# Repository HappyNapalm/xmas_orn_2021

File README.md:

# xmas_orn_2021
Repo for 2021 Ornament Design Files and Firmware

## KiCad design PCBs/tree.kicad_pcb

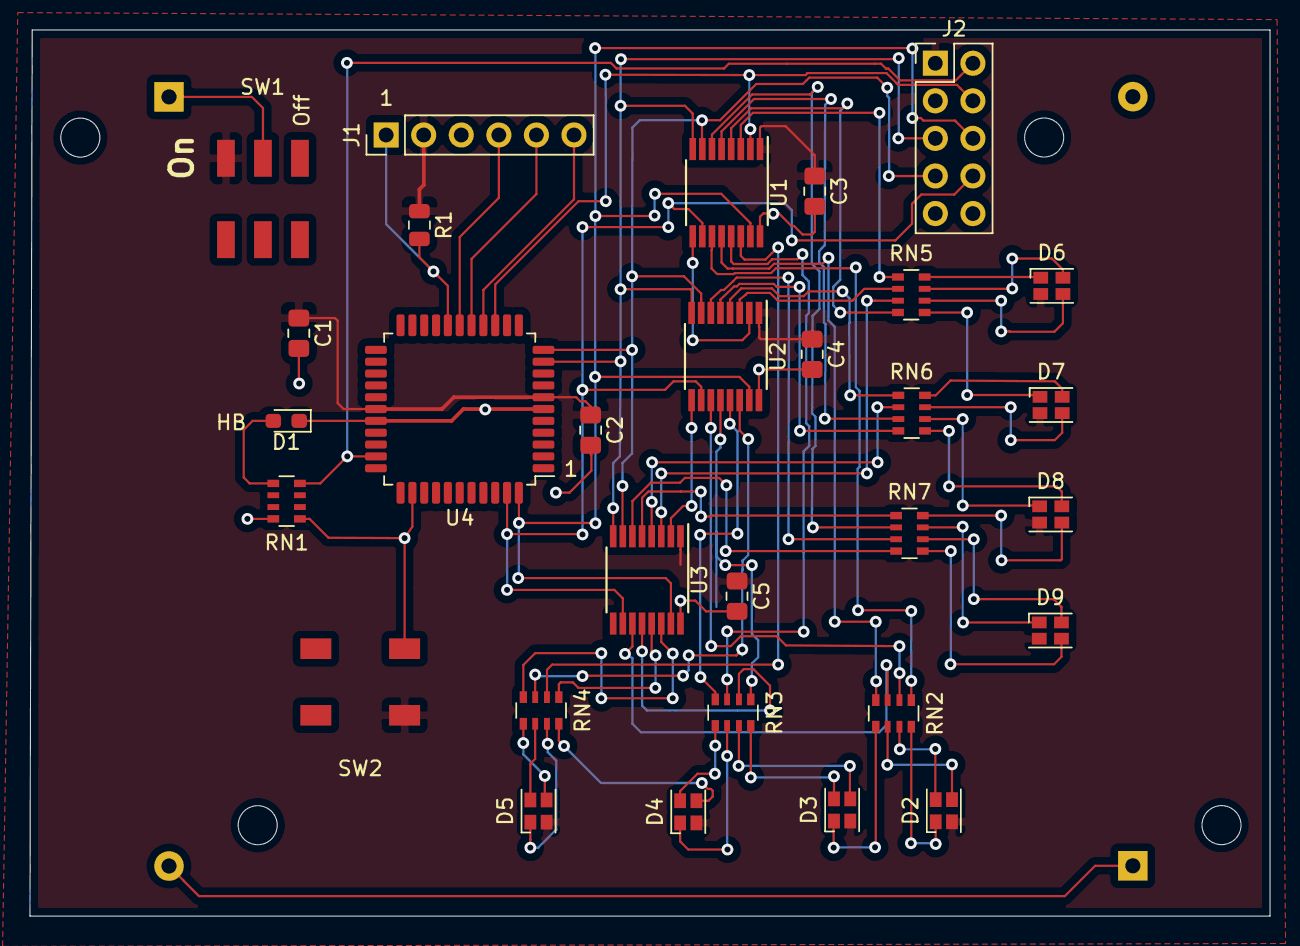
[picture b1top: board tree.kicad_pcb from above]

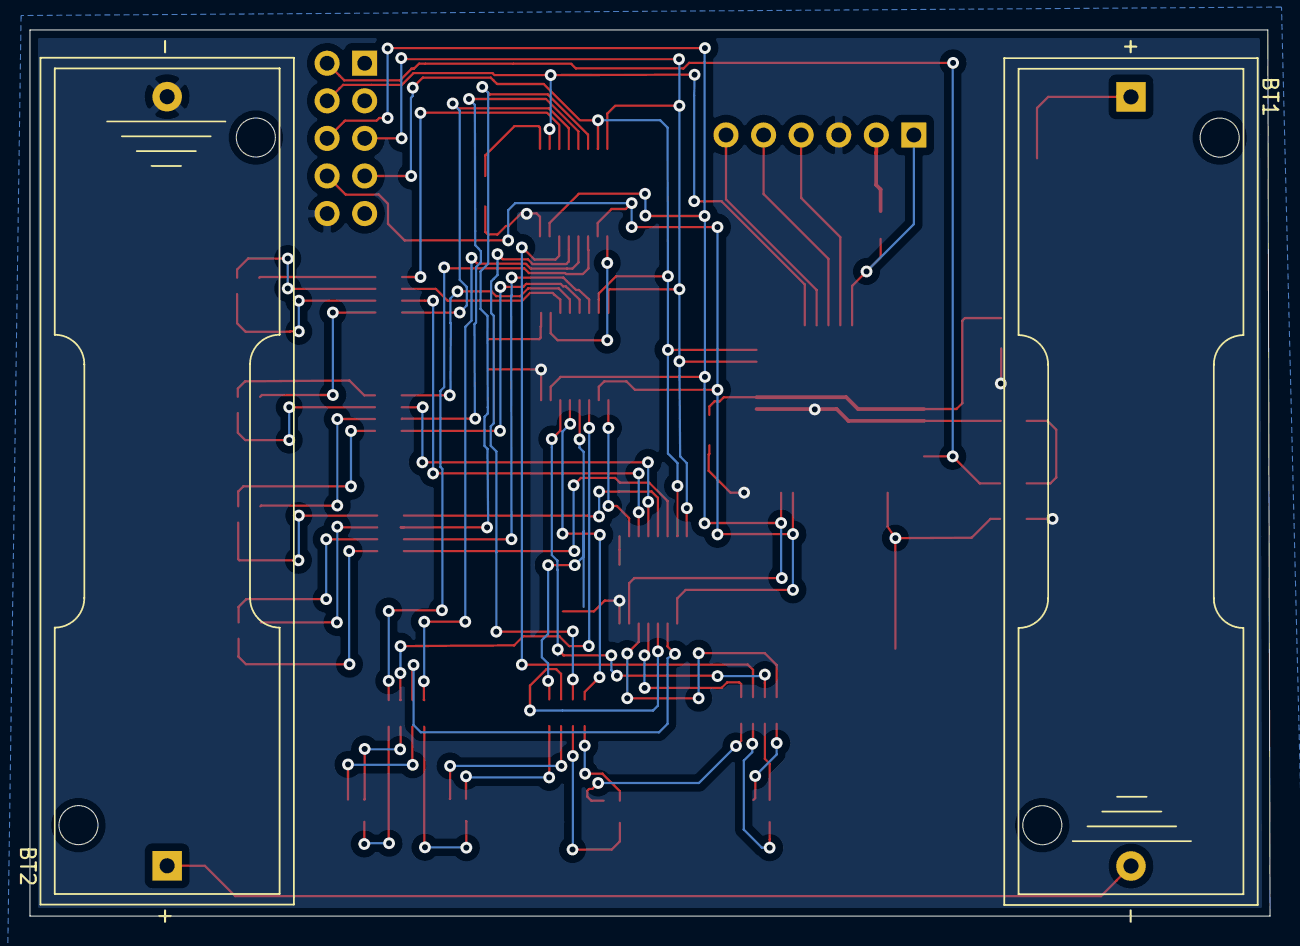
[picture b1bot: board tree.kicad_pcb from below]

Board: 2 copper layers, 83.8 x 59.9 mm, 32 parts (2 on the bottom side), 66 nets.

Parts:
BT1, BT2: Battery_Cell; BatteryHolder_Keystone_2460_1xAA
C1, C2, C3, C4, C5: C_Small; C_0805_2012Metric_Pad1.15x1.40mm_HandSolder
D1: LED; LED_0603_1608Metric_Pad1.05x0.95mm_HandSolder
D2, D3, D4, D5, D6, D7, D8, D9: LED_RGBA; LED_Cree-PLCC4_2x2mm_CW
J1: Conn_01x06_Female; PinHeader_1x06_P2.54mm_Vertical
J2: Conn_02x05_Odd_Even; PinHeader_2x05_P2.54mm_Vertical
R1: 10K; R_0805_2012Metric
RN1, RN2, RN3, RN4, RN5, RN6, RN7: R_Pack04; R_Array_Convex_4x0603
SW1: SW_Push_DPDT; JS202011SCQN
SW2: SW_SPST; LL3301FF065QJ
U1, U2, U3: Shift_Reg; TSSOP-16_4.4x5mm_P0.65mm
U4: pic18f45k20; LQFP-44_10x10mm_P0.8mm

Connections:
3v3: C1.1, C2.1, C3.1, C4.1, C5.1, D2.4, D3.4, D4.4, D5.4, D6.4, D7.4, D8.4, D9.4, J1.2, J2.1, R1.1, SW1.1, SW2.1, U1.1, U2.1, U3.1, U4.7, U4.28
B1: RN5.3, U3.3
B2: RN6.2, U3.4
B3: RN7.1, U3.5
B4: RN7.4, U3.6
B5: RN2.3, U3.11
B6: RN3.2, U3.12
B7: RN4.1, U3.13
B8: RN4.4, U3.14
BT1: RN1.1, SW2.2, U4.35
Blue_Data: U2.9, U3.2
G1: RN5.2, U2.3
G2: RN6.1, U2.4
G3: RN6.4, U2.5
G4: RN7.3, U2.6
G5: RN2.2, U2.11
G6: RN3.1, U2.12
G7: RN3.4, U2.13
G8: RN4.3, U2.14
GND: BT2.2, C1.2, C2.2, C3.2, C4.2, C5.2, D1.1, J1.3, J2.10, RN1.8, U1.16, U2.16, U3.16, U4.6, U4.29
Green_Data: U1.9, U2.2
HB: J2.2, RN1.4, U4.32
unnamed: BT1.1, SW1.2
unnamed: BT1.2, BT2.1
unnamed: D1.2, RN1.5
unnamed: D2.1, RN2.8
unnamed: D2.2, RN2.7
unnamed: D2.3, RN2.6
unnamed: D3.1, RN2.5
unnamed: D3.2, RN3.8
unnamed: D3.3, RN3.7
unnamed: D4.1, RN3.6
unnamed: D4.2, RN3.5
unnamed: D4.3, RN4.8
unnamed: D5.1, RN4.7
unnamed: D5.2, RN4.6
unnamed: D5.3, RN4.5
unnamed: D6.1, RN5.8
unnamed: D6.2, RN5.7
unnamed: D6.3, RN5.6
unnamed: D7.1, RN5.5
unnamed: D7.2, RN6.8
unnamed: D7.3, RN6.7
unnamed: D8.1, RN6.6
unnamed: D8.2, RN6.5
unnamed: D8.3, RN7.8
unnamed: D9.1, RN7.7
unnamed: D9.2, RN7.6
unnamed: D9.3, RN7.5
unnamed: J1.1, R1.2, U4.18
unnamed: J1.4, U4.17
unnamed: J1.5, U4.16
unnamed: J1.6, U4.15
R1: RN5.1, U1.3
R2: RN5.4, U1.4
R3: RN6.3, U1.5
R4: RN7.2, U1.6
R5: RN2.1, U1.11
R6: RN2.4, U1.12
R7: RN3.3, U1.13
R8: RN4.2, U1.14
Red_Data: J2.4, U1.2, U4.14
Shift_CLK: J2.6, U1.15, U2.15, U3.15, U4.44
Storage_CLK: J2.8, U1.10, U2.10, U3.10, U4.43
~MEM_RESET~: J2.7, U1.7, U2.7, U3.7, U4.11
~Output_Enable~: J2.5, U1.8, U2.8, U3.8, U4.10

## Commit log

2021-01-27 Copied over firmware and kicad libs I had previously worked on in other pic18f45k20 projects.
2021-01-28 Pre-Shift Reg Schematic
2021-01-31 Finished initial revision of schematic.
2021-02-07 Correct several footprint issues. Addressed symbol glitch. Some routing handled.
2021-02-08 Finished Bulk of routing. Reformated traces to use 6/6 mils as per board house rules.
2021-02-08 Adding LPC804 as ARM processor for this branch
2021-02-09 Addressing SWD header
2021-02-09 Added J2 for a debug/Logic probe header
2021-02-10 Laid out a board with debug header and LPC804
2021-02-14 Finished Layout, generated gerbers
2021-02-14 finished layout and generated gerbers
2021-02-27 Took a machete to the existing code base to remove ill fitting or non applicable code.
2021-02-27 tweaking LED code
